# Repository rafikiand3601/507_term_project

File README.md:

# ME 507 Term Project

Contributors:
* -Kevin Marshall

**How to use:**
* -Add/edit task objects that you are tasked with.
* -You must run the makefile from a linux machine OR CygWin.
* -Clone this repository to your cygwin folder.
* -Code is stored in the "code" folder.
* -Only modify the main project file to add tasks.
* -You can use the servo task as a template for how to add new tasks.
* -"make" in the code directory in a CygWin will compile your code.
* -Add new .cpp files to the makefile under "SOURCES"
* -"make install" will compile and put the code on the atmega(assuming
	AVRISP and UsbAsp are installed correctly).
* -Use PuTTy or Tera Term to communicate with the board via serial.
	baud = 9600, COMX, you will need to look in device manager for your
	COM number to connect to.
* **-DO NOT BURN FUSES ON THE ATMEGA**

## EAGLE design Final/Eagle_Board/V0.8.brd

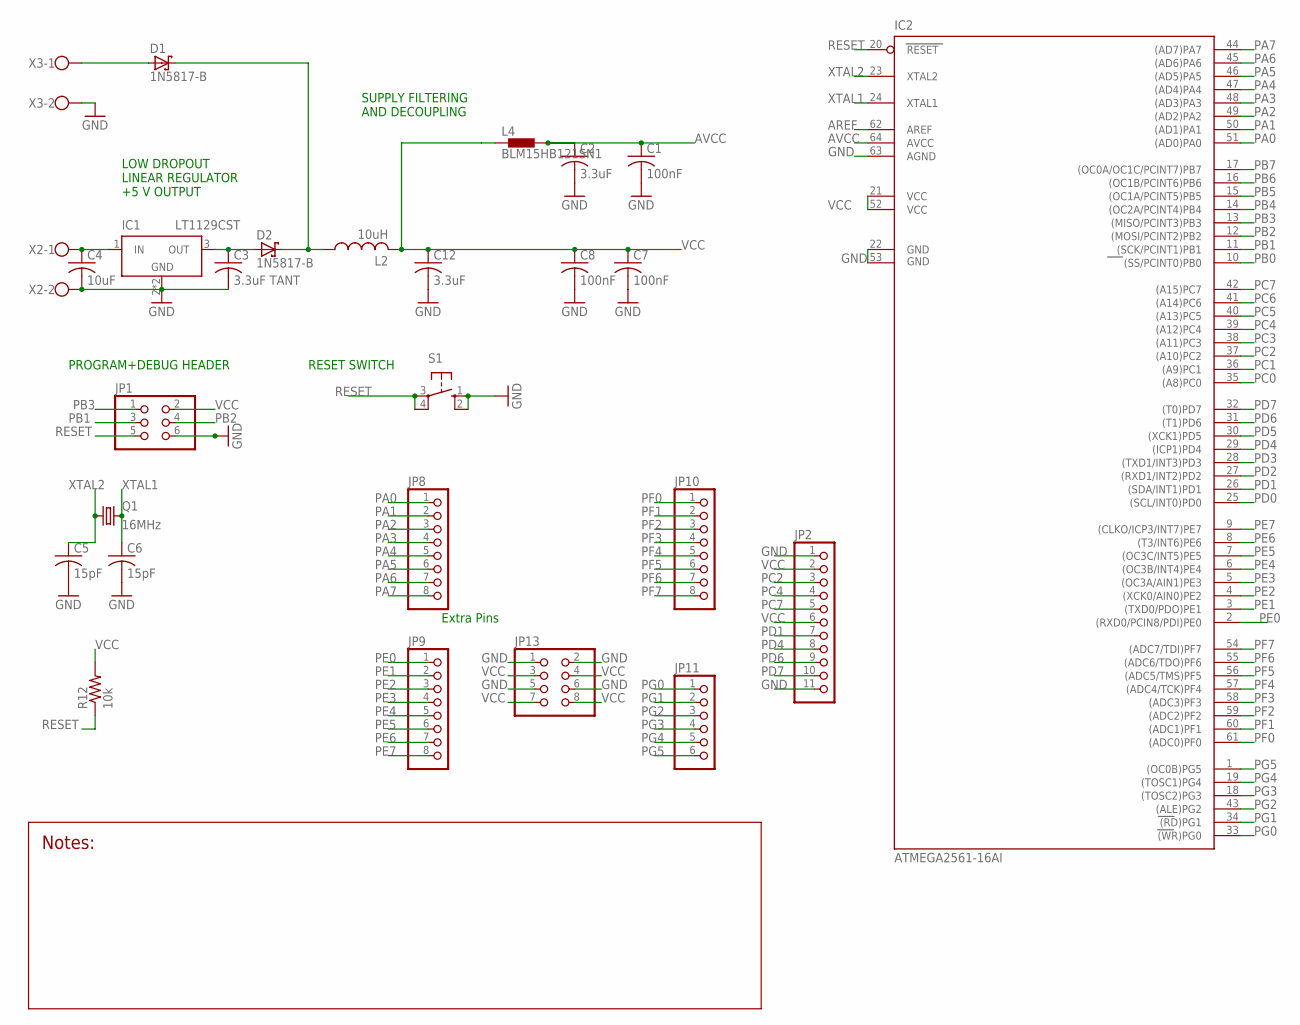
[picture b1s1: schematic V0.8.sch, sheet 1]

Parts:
C1, C7, C8: 100nF; C0805
C2, C12: 3.3uF; C0805
C3: 3.3uF TANT; C0805
C4: 10uF; C0805
C5, C6: 15pF; C0805
D1, D2: 1N5817-B; DO41-7.6
IC1: LT1129CST; SOT223
IC2: ATMEGA2561-16AI; TQFP64
JP1: PINHD-2X3; 2X03
JP2: PINHD-1X11; 1X11
JP8, JP9, JP10: PINHD-1X8; 1X08
JP11: PINHD-1X6; 1X06
JP13: PINHD-2X4; 2X04
L2: 10uH; L1812
L4: BLM15HB121SN1; 0402
Q1: 16MHz; HC49/S
R12: 10k; R0805
S1: 10-XX; B3F-10XX
X2, X3: W237-102

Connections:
AREF: IC2.62 (AREF)
AVCC: C1.1, C2.1, IC2.64 (AVCC), L4.2
GND: C1.2, C2.2, C3.2, C4.2, C5.2, C6.2, C7.2, C8.2, C12.2, IC1.2 (GND), IC1.4 (GND), IC2.22 (GND), IC2.53 (GND1), IC2.63 (AGND), JP1.6, JP2.1, JP2.11, JP13.1, JP13.2, JP13.5, JP13.6, S1.1 (S), S1.2 (S1), X2.2, X3.2; also elsewhere on the board
unnamed: D1.C, D2.C, L2.1
unnamed: D1.A, X3.1
PA0: IC2.51 ((AD0)PA0), JP8.1
PA1: IC2.50 ((AD1)PA1), JP8.2
PA2: IC2.49 ((AD2)PA2), JP8.3
PA3: IC2.48 ((AD3)PA3), JP8.4
PA4: IC2.47 ((AD4)PA4), JP8.5
PA5: IC2.46 ((AD5)PA5), JP8.6
PA6: IC2.45 ((AD6)PA6), JP8.7
PA7: IC2.44 ((AD7)PA7), JP8.8
PB0: IC2.10 ((SS/PCINT0)PB0)
PB1: IC2.11 ((SCK/PCINT1)PB1), JP1.3
PB2: IC2.12 ((MOSI/PCINT2)PB2), JP1.4
PB3: IC2.13 ((MISO/PCINT3)PB3), JP1.1
PB4: IC2.14 ((OC2A/PCINT4)PB4); also elsewhere on the board
PB5: IC2.15 ((OC1A/PCINT5)PB5); also elsewhere on the board
PB6: IC2.16 ((OC1B/PCINT6)PB6); also elsewhere on the board
PB7: IC2.17 ((OC0A/OC1C/PCINT7)PB7); also elsewhere on the board
PC0: IC2.35 ((A8)PC0); also elsewhere on the board
PC1: IC2.36 ((A9)PC1); also elsewhere on the board
PC2: IC2.37 ((A10)PC2), JP2.3; also elsewhere on the board
PC3: IC2.38 ((A11)PC3); also elsewhere on the board
PC4: IC2.39 ((A12)PC4), JP2.4; also elsewhere on the board
PC5: IC2.40 ((A13)PC5); also elsewhere on the board
PC6: IC2.41 ((A14)PC6); also elsewhere on the board
PC7: IC2.42 ((A15)PC7), JP2.5
PD0: IC2.25 ((SCL/INT0)PD0)
PD1: IC2.26 ((SDA/INT1)PD1), JP2.7
PD2: IC2.27 ((RXD1/INT2)PD2); also elsewhere on the board
PD3: IC2.28 ((TXD1/INT3)PD3); also elsewhere on the board
PD4: IC2.29 ((ICP1)PD4), JP2.8
PD5: IC2.30 ((XCK1)PD5)
PD6: IC2.31 ((T1)PD6), JP2.9
PD7: IC2.32 ((T0)PD7), JP2.10
PE0: IC2.2 ((RXD0/PCIN8/PDI)PE0), JP9.1
PE1: IC2.3 ((TXD0/PDO)PE1), JP9.2
PE2: IC2.4 ((XCK0/AIN0)PE2), JP9.3
PE3: IC2.5 ((OC3A/AIN1)PE3), JP9.4
PE4: IC2.6 ((OC3B/INT4)PE4), JP9.5
PE5: IC2.7 ((OC3C/INT5)PE5), JP9.6
PE6: IC2.8 ((T3/INT6)PE6), JP9.7
PE7: IC2.9 ((CLKO/ICP3/INT7)PE7), JP9.8
PF0: IC2.61 ((ADC0)PF0), JP10.1
PF1: IC2.60 ((ADC1)PF1), JP10.2
PF2: IC2.59 ((ADC2)PF2), JP10.3
PF3: IC2.58 ((ADC3)PF3), JP10.4
PF4: IC2.57 ((ADC4/TCK)PF4), JP10.5
PF5: IC2.56 ((ADC5/TMS)PF5), JP10.6
PF6: IC2.55 ((ADC6/TDO)PF6), JP10.7
PF7: IC2.54 ((ADC7/TDI)PF7), JP10.8
PG0: IC2.33 ((WR)PG0), JP11.1
PG1: IC2.34 ((RD)PG1), JP11.2
PG2: IC2.43 ((ALE)PG2), JP11.3
PG3: IC2.18 ((TOSC2)PG3), JP11.4
PG4: IC2.19 ((TOSC1)PG4), JP11.5
PG5: IC2.1 ((OC0B)PG5), JP11.6
RESET: IC2.20 (RESET), JP1.5, R12.1, S1.3, S1.4 (P1)
VCC: C7.1, C8.1, C12.1, IC2.21 (VCC), IC2.52 (VCC1), JP1.2, JP2.2, JP2.6, JP13.3, JP13.4, JP13.7, JP13.8, L2.2, L4.1, R12.2; also elsewhere on the board
VIN: C4.1, IC1.1 (IN), X2.1
VOUT: C3.1, D2.A, IC1.3 (OUT)
XTAL1: C6.1, IC2.24 (XTAL1), Q1.2
XTAL2: C5.1, IC2.23 (XTAL2), Q1.1

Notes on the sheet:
RESET SWITCH
LOW DROPOUT LINEAR REGULATOR +5 V OUTPUT
SUPPLY FILTERING AND DECOUPLING
PROGRAM+DEBUG HEADER
Extra Pins

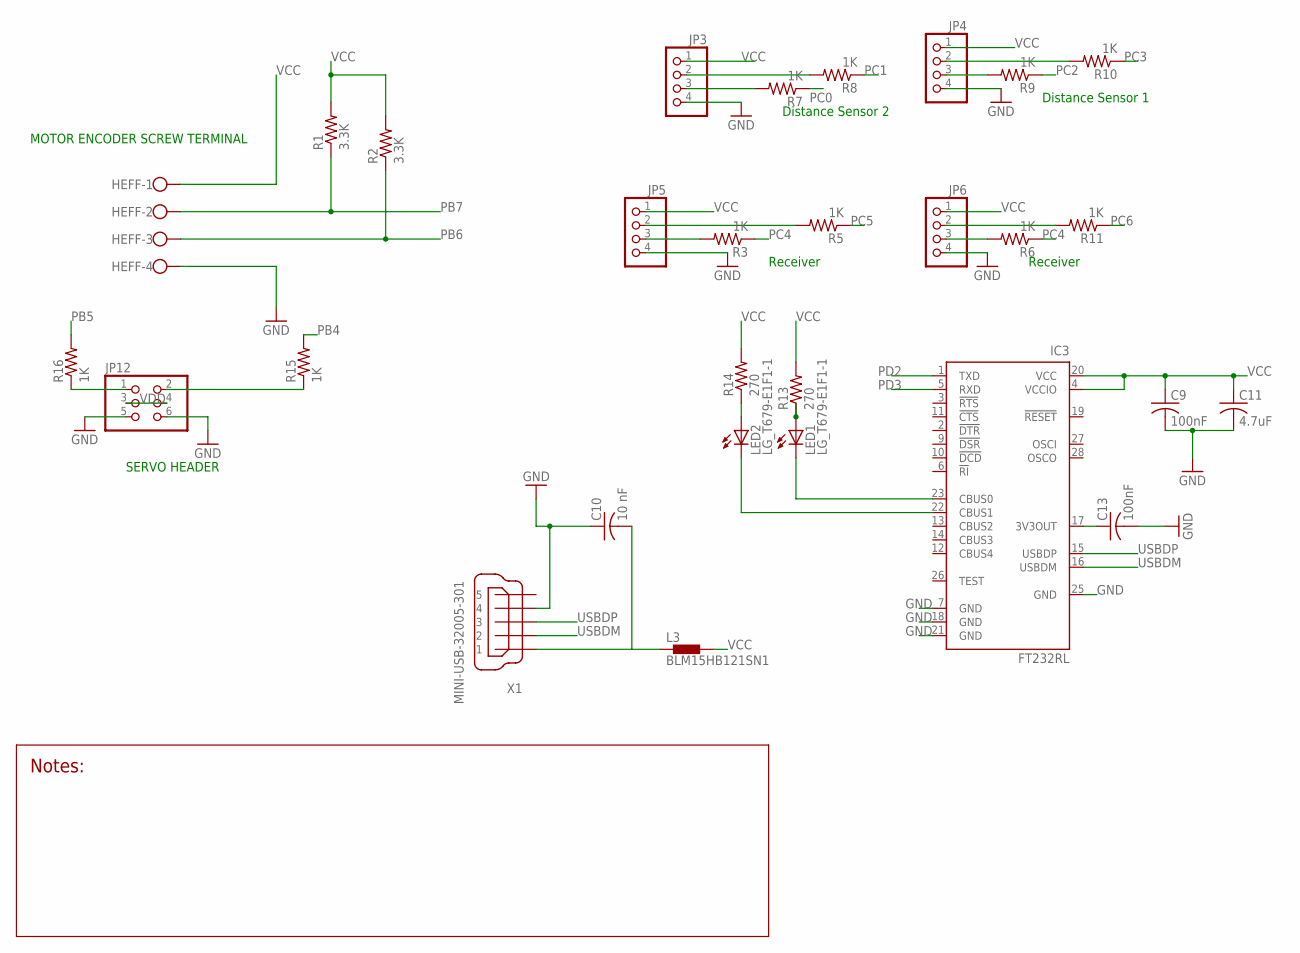
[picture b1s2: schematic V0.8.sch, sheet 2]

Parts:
C9, C13: 100nF; C0805
C10: 10 nF; C0805
C11: 4.7uF; C0805
HEFF: W237-4
IC3: FT232RL; SSOP28
JP3, JP4, JP5, JP6: PINHD-1X4; 1X04
JP12: PINHD-2X3; 2X03
L3: BLM15HB121SN1; 0402
LED1, LED2: LG_T679-E1F1-1; PLCC2
R1, R2: 3.3K; R0805
R3, R5, R6, R7, R8, R9, R10, R11, R15, R16: 1K; R0805
R13, R14: 270; R0805
X1: MINI-USB-32005-301; 32005-301

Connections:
GND: C9.2, C10.1, C11.2, C13.2, HEFF.4, IC3.7 (GND), IC3.18 (GND), IC3.21 (GND), IC3.25 (GND), JP3.4, JP4.4, JP5.4, JP6.4, JP12.5, JP12.6, X1.4; also elsewhere on the board
unnamed: JP4.3, R9.2
unnamed: JP5.3, R3.2
unnamed: JP6.3, R6.2
unnamed: JP5.2, R5.2
unnamed: JP3.2, R8.2
unnamed: JP3.3, R7.2
unnamed: JP4.2, R10.2
unnamed: JP6.2, R11.2
unnamed: C10.2, L3.1, X1.1
unnamed: C13.1, IC3.17 (3V3OUT)
unnamed: IC3.23 (CBUS0), LED1.C
unnamed: LED1.A, R13.1
unnamed: JP12.2, R15.1
unnamed: IC3.22 (CBUS1), LED2.C
unnamed: LED2.A, R14.1
unnamed: JP12.1, R16.1
PB4: R15.2; also elsewhere on the board
PB5: R16.2; also elsewhere on the board
PB6: HEFF.3, R2.1; also elsewhere on the board
PB7: HEFF.2, R1.1; also elsewhere on the board
PC0: R7.1; also elsewhere on the board
PC1: R8.1; also elsewhere on the board
PC2: R9.1; also elsewhere on the board
PC3: R10.1; also elsewhere on the board
PC4: R3.1, R6.1; also elsewhere on the board
PC5: R5.1; also elsewhere on the board
PC6: R11.1; also elsewhere on the board
PD2: IC3.1 (TXD); also elsewhere on the board
PD3: IC3.5 (RXD); also elsewhere on the board
USBDM: IC3.16 (USBDM), X1.2
USBDP: IC3.15 (USBDP), X1.3
VCC: C9.1, C11.1, HEFF.1, IC3.4 (VCCIO), IC3.20 (VCC), JP3.1, JP4.1, JP5.1, JP6.1, L3.2, R1.2, R2.2, R13.2, R14.2; also elsewhere on the board
VDD: JP12.3, JP12.4

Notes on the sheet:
SERVO HEADER
MOTOR ENCODER SCREW TERMINAL
Distance Sensor 2
Distance Sensor 1
Receiver

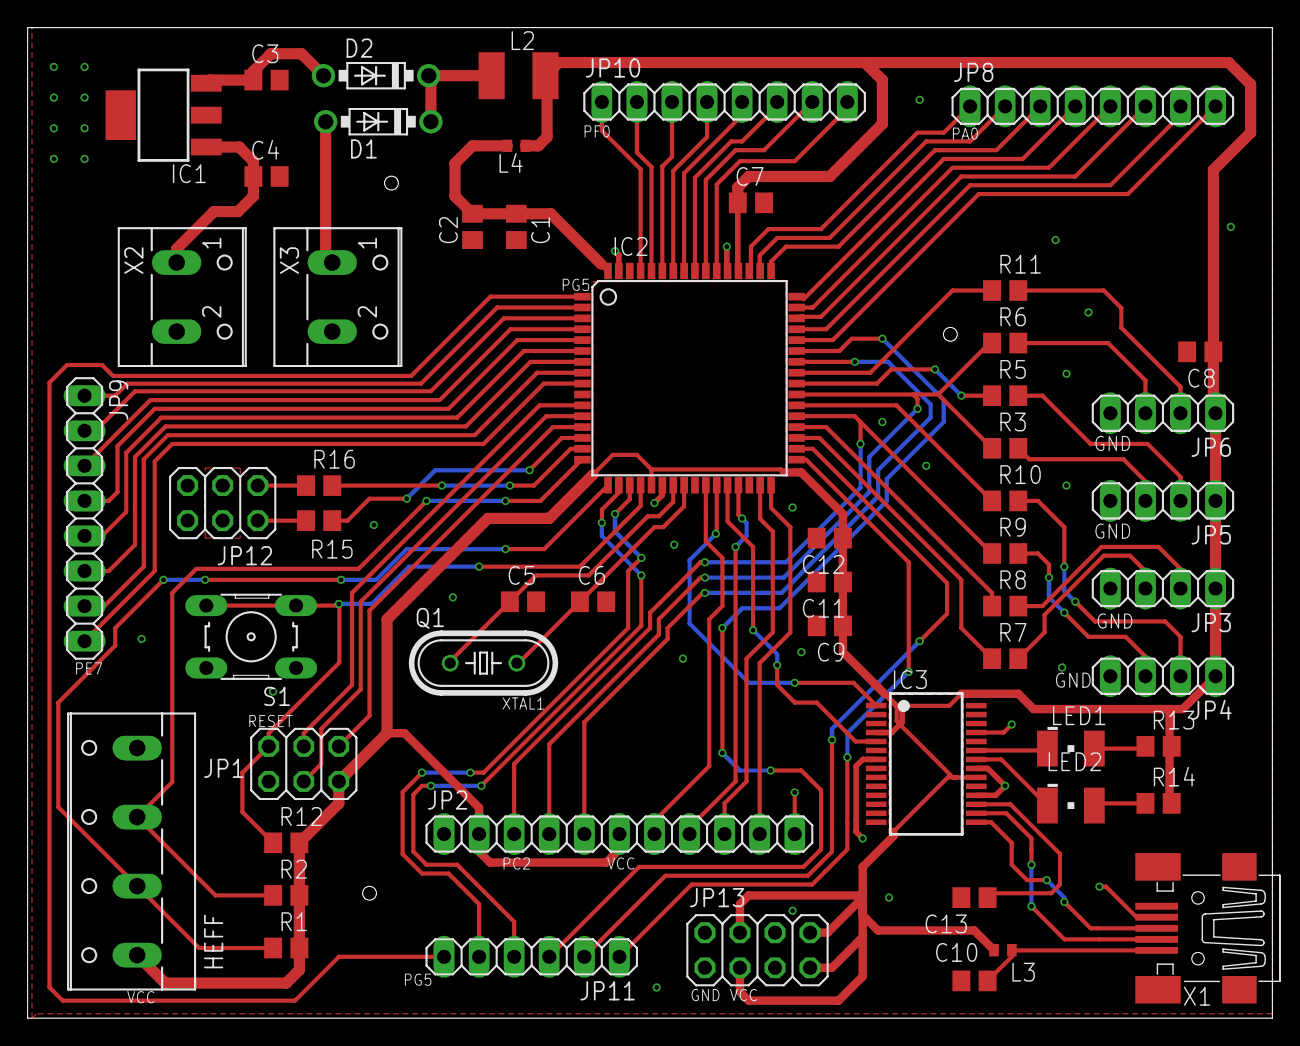
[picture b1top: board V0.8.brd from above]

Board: 2 copper layers, 90.2 x 71.7 mm, 56 parts (0 on the bottom side), 80 nets.

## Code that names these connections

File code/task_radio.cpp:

//**************************************************************************************
/** @file task_radio.cpp
 *    This file contains code to control the transciever for the ME 507 term project. 
 *
 *  Revisions:
 *    @li 12-1-2018 KM file created to operate the transciever.
 *    @li 12-9-2018 KM last planned edit.
 *  
 *  License:
 *	This code is based on Prof. JR Ridgely's FreeRTOS CPP example code. The FreeRTOS
 *	framework is used, but the tasks are a product of our 507 group. Since the original
 *	code used the LGPL, our code will also use the LGPL.
 *		THIS SOFTWARE IS PROVIDED BY THE COPYRIGHT HOLDERS AND CONTRIBUTORS "AS IS"
 *		AND	ANY EXPRESS OR IMPLIED WARRANTIES, INCLUDING, BUT NOT LIMITED TO, THE
 * 		IMPLIED 	WARRANTIES OF MERCHANTABILITY AND FITNESS FOR A PARTICULAR PURPOSE
 * 		ARE DISCLAIMED. IN NO EVENT SHALL THE COPYRIGHT OWNER OR CONTRIBUTORS BE
 * 		LIABLE FOR ANY DIRECT, INDIRECT, INCIDENTAL, SPECIAL, EXEMPLARY, OR CONSEQUEN-
 * 		TIAL DAMAGES (INCLUDING, BUT NOT LIMITED TO, PROCUREMENT OF SUBSTITUTE GOODS
 * 		OR SERVICES; LOSS OF USE, DATA, OR PROFITS; OR BUSINESS INTERRUPTION) HOWEVER
 * 		CAUSED AND ON ANY THEORY OF LIABILITY, WHETHER IN CONTRACT, STRICT LIABILITY,
 * 		OR TORT (INCLUDING NEGLIGENCE OR OTHERWISE) ARISING IN ANY WAY OUT OF THE USE
 * 		OF THIS SOFTWARE, EVEN IF ADVISED OF THE POSSIBILITY OF SUCH DAMAGE. */
//**************************************************************************************



#include <avr/io.h>                         // Port I/O for SFR's
#include <avr/wdt.h>                        // Watchdog timer header


#include "task_radio.h"                     // Header for this file






//-------------------------------------------------------------------------------------
/** This constructor creates a new data acquisition task. Its main job is to call the
 *  parent class's constructor which does most of the work.
 *  @param a_name A character string which will be the name of this task
 *  @param a_priority The priority at which this task will initially run (default: 0)
 *  @param a_stack_size The size of this task's stack in bytes 
 *                      (default: configMINIMAL_STACK_SIZE)
 *  @param p_ser_dev A pointer to the serial port which writes debugging info. 
 */

task_radio::task_radio (const char* a_name, 
					  unsigned portBASE_TYPE a_priority, 
					  size_t a_stack_size,
					  emstream* p_ser_dev
					 )
	: TaskBase (a_name, a_priority, a_stack_size, p_ser_dev)
{
	// Nothing is done in the body of this constructor. All the work is done in the
	// call to the frt_task constructor on the line just above this one
}


//-------------------------------------------------------------------------------------
/** This task handles sending messages over the transciever to the transponder
 */

void task_radio::run (void)
{

	// This is an infinite loop; it runs until the power is turned off. There is one 
	// such loop inside the code for each task
	for (;;)
	{
		// Run the finite state machine. The variable 'state' is kept by parent class
		switch (state)
		{
			// - - - - - - - - - - - - - - - - - - - - - - - - - - - - - - - - - - - -
			// State 0, setup radio transciever
			case (0):
				to_address[0] = 0x00;
				to_address[1] = 0x01;
				//setup_rf();
				
				init_spi ();
				_delay_us (10);
				*p_serial << get_reg(STATUS) << endl;
				//write_byte (R_REGISTER + STATUS);
				
				state = 1;
				break; // End of state 0

			// - - - - - - - - - - - - - - - - - - - - - - - - - - - - - - - - - - - -
			// Run control actions
			case (1):
				// Wait for ping flag to be set
				if (p_rf_ping->get () == 1)
				{
					p_rf_ping->put (0);
					state = 2;
				}
				break;
				
			case (2):
				// Send ping signal
				*p_serial << get_reg(STATUS) << endl;
				
				uint8_t name [5];
				name[0] = 'n';
				name[1] = 'o';
				name[2] = 'd';
				name[3] = 'e';
				name[4] = '1';
				//int i;
				// Set up transmitter address
				read_or_write (W, TX_ADDR, name, 5);
				
				// Set as transmitter, and power on
				uint8_t val [2];
				val[0] = 0b00000010;
				read_or_write (W, CONFIG, val, 1);
				
				_delay_ms(2);
				
				// Send message
				uint8_t data[2];
				data[0] = 0x00;
				data[1] = 'a';
				transmit(data);
				
				state = 1;
				break;
				
				
			// - - - - - - - - - - - - - - - - - - - - - - - - - - - - - - - - - - - - - -
			// We should never get to the default state. If we do, complain and restart
			default:
				*p_serial << PMS ("Illegal state! Resetting AVR") << endl;
				wdt_enable (WDTO_120MS);
				for (;;) ;
				break;

		} // End switch state

		runs++;                             // Increment counter for debugging

		// No matter the state, wait for approximately a millisecond before we 
		// run the loop again. This gives lower priority tasks a chance to run
		delay_ms (1);
	}
}



//----------------------------------------------------------------------------------



/** @brief A method to initialize the SPI interface to the RF module.
  * @details This method sets the correct SPI pins as inputs and outputs, and sets
  * their states so that the SPI interface can connect to the RF module.
  */
void task_radio::init_spi (void)
{
	// Set MOSI(PB2) and SCK(PB1) output, MISO(PB3) input, CSN(PB0) output
	DDRB |= (1 << PB2) | (1 << PB1) | (1 << PB0);
	DDRB &= ~(1 << PB3);
	// Set CE(PE3) as output
	DDRE |= (1 << PE3);

	// Enable SPI as master
	SPCR |= (1 << SPE) | (1 << MSTR) | (1 << SPR1);
	
	// CSN high to start with
	PORTB |= (1 << PB0);
	// CE low to start with
	PORTE &= ~(1 << PE3);
}


/** @brief A method to send a byte to the RF module.
  * @details This method uses the SPI data register on our microcontroller to
  * send a byte of information to the RF module.
  * @param c_data A char byte that is to be sent to the RF module.
  * @return SPDR The char data that was sent to the RF module.
  */
char task_radio::write_byte (char c_data)
{
	// Load byte to data register
	SPDR = c_data;
	
	// Wait for transmit to finish
	while(!(SPSR & (1 << SPIF))) ;
	
	return SPDR;
}

/** @brief A method to get the value of a register on the RF module.
  * @details This method uses the SPI data register on our microcontroller to
  * send a byte of information to the RF module.
  * @param reg A uint8_t value that corresonds to the desired register.
  * @return reg The uint8_t data that was contained in the desired register
  * RF module.
  */
uint8_t task_radio::get_reg (uint8_t reg)
{
	_delay_us (10);
	// Set CSN low
	PORTB &= ~(1 << PB0);
	_delay_us (10);
	// Set nRF to reading mode
	write_byte (R_REGISTER + reg);
	_delay_us (10);
	reg = write_byte (NOP);
	_delay_us (10);
	// Set CSN high
	PORTB |= (1 << PB0);
	return reg;
}


/** @brief A method to write data to the RF module.
  * @details This method uses the SPI data register on our microcontroller to
  * send a byte of information to the RF module.
  * @param ReadWrite A uint8_t character that corresponds to either a value
  * being written to or read from the RF module.
  * @param reg A uint8_t value that corresponds to the register of the RF
  * module that is being modified.
  * @param val A pointer to the values array that are to written to the RF
  * module.
  * @param antVal A uint8_t value that signifies the number of bytes to write
  * to the RF module.
  * @return ret The array of uint8_t* data that was sent to the RF module.
  */
uint8_t *task_radio::read_or_write (uint8_t ReadWrite, uint8_t reg, uint8_t *val, uint8_t antVal)
{
	if (ReadWrite == W)
	{
		reg = W_REGISTER + reg;
	}
	
	static uint8_t ret [32];
	
	_delay_us (10);
	// Set CSN low
	PORTB &= ~(1 << PB0);
	_delay_us (10);
	write_byte (reg);
	_delay_us (10);
	
	int i;
	for(i = 0; i < antVal; i++)
	{
		if (ReadWrite == R && reg != W_TX_PAYLOAD)
		{
			ret [i] = write_byte (NOP);
			_delay_us (10);
		}
		else
		{
			write_byte (val [i]);
			_delay_us (10);
		}
	}
	
	// Set CSN high
	PORTB |= (1 << PB0);
	return ret;
}

/** @brief A method to transmit a character array with the RF module.
  * @details This method uses the read_or_write method to transmit an array
  * of characters using the RF module.
  * @param W_buff A uint8_t* pointer to an array which is to be sent to
  * the RF module.
  */
void task_radio::transmit (uint8_t *W_buff)
{
	read_or_write (R, FLUSH_TX, W_buff, 0);
	read_or_write (R, W_TX_PAYLOAD, W_buff, 2);
	
	_delay_ms(10);
	// Set CE high
	PORTE |= (1 << PE3);
	_delay_ms(10);
	// Set CE low
	PORTE &= ~(1 << PE3);
}
	

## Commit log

2018-11-30 PCB Files Added
    Added Eagle PCB files
2018-11-30 Added Readme
    Basic instructions added in readme
2018-11-30 Rearranged file structure, readme
    -Moved files so that libraries are included in the repo
    -Basic instructions added in readme
2018-11-30 Updated Readme
    -explaned code folder
    -explained serial settings
2018-11-30 Readme
    Playing with readme
2018-11-30 Update README.md
    playing readme
2018-12-01 Added Pinout, PWM tasks
    -Added pinout list as txt file
    -Revised servo control task. hopefully it works this time
    -Wrote ESC control task
2018-12-01 Added RF24 Arduino code
    -added code that uses the arduino with an RF24 module and an ultrasonic emmiter as the transponder
    -will need to verify pin assignments
2018-12-01 Update main.cpp
    Added all tasks
2018-12-01 USR1
2018-12-01 Update main.cpp
    added tasks
2018-12-02 Servo and Motor Drivers
    Servo and Motor can now be controlled!
2018-12-02 Worked on tasks
    -added radio task
    -added shared variables for motor, servo, and encoder communication
2018-12-02 Got RF libs to compile
    -setup nRF24 libraries to work with c++
    -got a basic framework of the nRF module setup
    -needs testing and pin setup
2018-12-02 RF stuff, control flags
    -set up RF ping via user task
    -set up flag to run and stop car with flag controlled from user task
    -set up arduino RF module testing
2018-12-03 Input capture isr
2018-12-03 Wiring/RF
    -ESC wired, runs motor
    -Updated ESC to use 16 bit timer
    -Worked on RF(issues with SPI loop and mem allocation)
    -Tested user input commands
2018-12-03 Car Drives, more RF testing
    -Adjusted the driving speed of the car. It stutters when first moving, then moves quickly. It may move too fast for our uses.
    -added rf_names header, and wrote code to open an SPI connection to talk to the rf module
    -needs testing to see if the rf module works with this setup
2018-12-04 Working Input Capture
    Working toggle on input capture, distance sensor not working
2018-12-04 Working Distance Sensor
2018-12-04 RF Testing
    -Some stuff works!
    -Got Arduino Transponder and test send sketches to talk to each other
    -Adjusted RF code to use address and characters that the transponder will be able to read
2018-12-04 Revert "RF Testing"
    This reverts commit 34e096beb89c867c664e7fad2c675e84bdbb715d.
2018-12-04 Revert "Merge branch 'master' into test"
    This reverts commit 08d974290f0eacfa6346b2d0e05b6fb04a6d9e9e, reversing
    changes made to 34e096beb89c867c664e7fad2c675e84bdbb715d.
2018-12-04 Revert "Revert "Merge branch 'master' into test""
    This reverts commit 47d73f979bb49250bc10f62b8bd0fbe40562feb2.
2018-12-04 Revert "Revert "RF Testing""
    This reverts commit 8d0f6a0028a00a53860d883182972c1b9e84690c.
2018-12-04 Revert "Revert "Merge branch 'master' into test""
    This reverts commit 38e4a83651b47f1c00b2d968746ebdcd0d74dc90.
2018-12-04 RF testing again
    does this work?
2018-12-04 Working object avoidance
2018-12-05 Revert "ss"
    This reverts commit 17a1e255b986e14d028bb78ae006cd982d9215db.
2018-12-05 Revert "Merge branch 'master' of https://github.com/rafikiand3601/507_term_project"
    This reverts commit 9bd1b3da2168fc7a1db09de64fa1cbc8971d2c2f, reversing
    changes made to 795b63e63d5a64795402b937b3c169190ba6a26a.
2018-12-10 Cleaning up code
    -Rewrote liscense disclaimer
    -need to get doxygen documented
2018-12-10 Documentation done for my code
    Documentation of Kevin's code is done
2018-12-10 Documentation
2018-12-10 Documentation2
2018-12-11 Doc update
2018-12-11 Doxygen done
